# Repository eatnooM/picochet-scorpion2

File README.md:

# Picochet-Scorpion2

A dedicated microcontroller board for use with the OpenFIRE firmware, made to fit in the wonderfully comfortable Blaze Scorpion 2 shell

Picking up where the Picochet-TC1 left off, this board removes the solenoid feedback circuit and adds support for a few extra goodies that might make sense to add in a Scorpion 2, such as Neopixel LED (I have a 3D printable light pipe that takes the place of one of the wheels to adjust the laser in the stock Scorpion 2) and an analog stick (no plans to physically accommodate this in the shell but if you reckon you can make one fit, go nuts)

##  BOM

I'll copy the BOM into a nice table once it's settled.

## Thanks

OpenFIRE project - https://openfirelightgun.org/

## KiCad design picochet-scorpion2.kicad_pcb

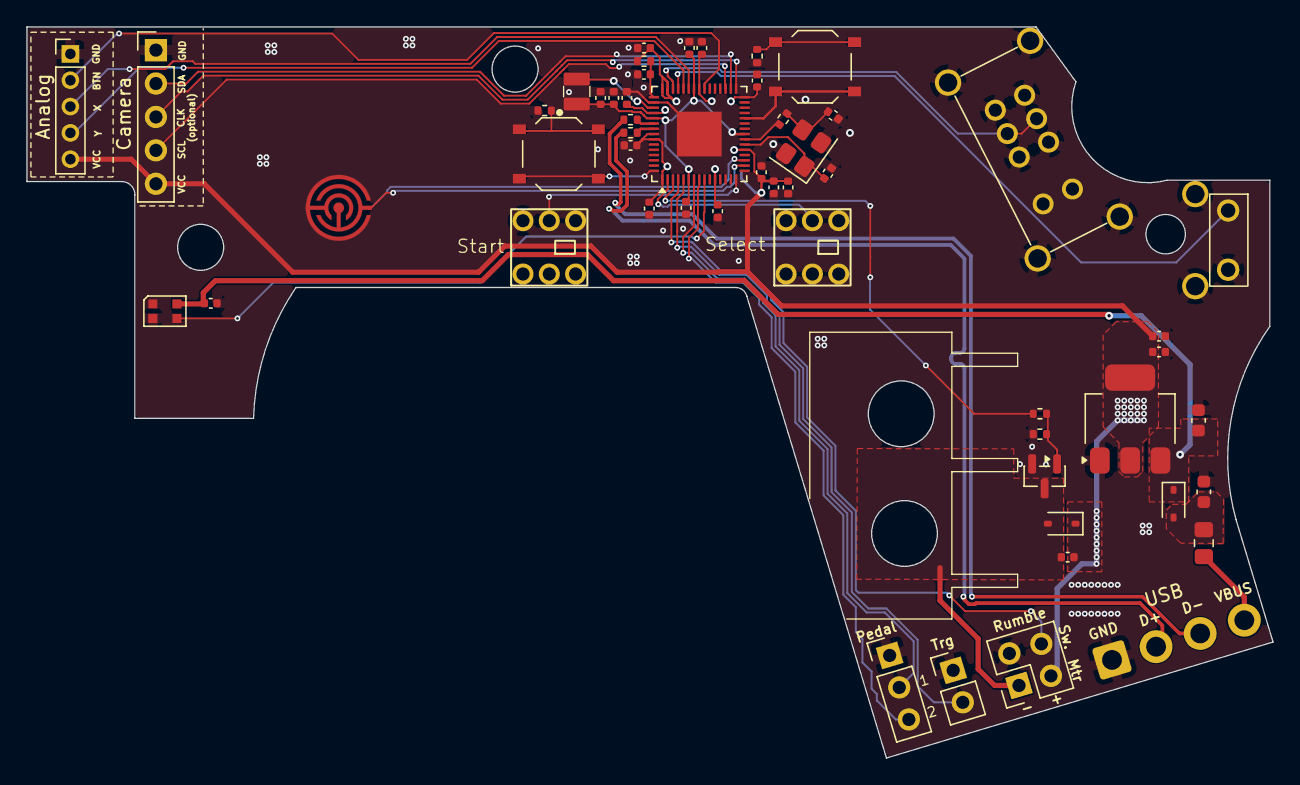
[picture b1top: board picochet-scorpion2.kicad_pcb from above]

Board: 2 copper layers, 94.7 x 55.6 mm, 54 parts (1 on the bottom side), 39 nets.

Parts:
C1, C21: 10uF; C_0603_1608Metric
C3, C4: 30pF; C_0402_1005Metric
C5, C19: 10uF; C_0402_1005Metric
C6, C7, C9, C10: 4.7uF; C_0402_1005Metric
C8, C11, C12, C13, C14, C15, C16, C17, C18, C20, C23, C24, C25: 100nF; C_0402_1005Metric
D1: 1N5819WS; D_SOD-323
D2: BAT43WS; D_SOD-323
D3: WS2812B-2020; LED_WS2812B-2020_PLCC4_2.0x2.0mm
F1: PPTC-6V 500mA; Fuse_0805_2012Metric_Pad1.15x1.40mm_HandSolder
J1: Conn_02x02; PinHeader_2x02_P2.54mm_Vertical
J2: Conn_01x02; PinHeader_1x02_P2.54mm_Vertical
J3: Conn_01x04; USB-PTH-2.5MMOD-3.5mmSpacing
J4: Conn_01x03; PinHeader_1x03_P2.54mm_Vertical
J6: Conn_01x05; PinHeader_1x05_P2.54mm_Vertical
J8: Conn_01x05; PinHeader_1x05_P2.00mm_Vertical
L1: AOTA-B201610S3R3; L_0806_PolarityMark
Q1: AO3400A; SOT-23
R2, R4, R6: 1k; R_0402_1005Metric
R5, R7, R8: 33; R_0402_1005Metric
R14: 100; R_0402_1005Metric
R15: 10k; R_0402_1005Metric
SW1, SW2: SW_Push; SW_Push_1P1T_XKB_TS-1187A
SW3: SW_SP3T_Shielded; ModeSwitch-DP3T-MountingPoints
SW4, SW5: SW_Push; RubberDomeContacts-D5mm
SW6: SW_Push; ModeSwitch-Momentary
SW7, SW8: SW_DPDT; Switch-DPDT-5.8x5.8mm
U1: RP2354A; QFN-60-1EP_7x7mm_P0.4mm_EP3.4x3.4mm
U2: AMS1117-3.3; SOT-223-3_TabPin2
Y1: X322512MSB4SI; Crystal_SMD_3225-4Pin_3.2x2.5mm

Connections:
+1V1: C7.1, C8.2, C10.1, C11.2, L1.1, U1.6 (DVDD), U1.23 (DVDD), U1.39 (DVDD), U1.50 (VREG_FB)
+3V3: C5.1, C6.1, C12.1, C13.1, C14.1, C15.1, C16.1, C17.1, C18.1, C19.1, C20.1, C24.1, C25.2, D2.1 (K), J1.3, J6.5, J8.5, R5.1, U1.1 (IOVDD), U1.11 (IOVDD), U1.20 (IOVDD), U1.30 (IOVDD), U1.38 (IOVDD), U1.44 (ADC_AVDD), U1.45 (IOVDD), U1.49 (VREG_VIN), U1.53 (USB_OTP_VDD), U1.54 (QSPI_IOVDD), U2.2 (VO)
+5V: C21.1, D1.2 (A), F1.2
/AXIS_X: J8.3, U1.40 (GPIO26/ADC0)
/AXIS_Y: J8.4, U1.41 (GPIO27/ADC1)
/CAM_CLK: J6.3, U1.31 (GPIO19)
/CAM_SCL: J6.4, U1.33 (GPIO21)
/CAM_SDA: J6.2, U1.32 (GPIO20)
/LED_DI: D3.3 (DIN), U1.9 (GPIO6)
/RMB_GND: C24.2, D2.2 (A), J1.1, Q1.3 (D)
/RUMBLE: R14.1, U1.3 (GPIO1)
/USB_D+: J3.2, R7.1
/USB_D-: J3.3, R8.1
/VREG_LX: L1.2, U1.48 (VREG_LX)
/~AUTOFIRE: SW3.3, U1.43 (GPIO29/ADC3)
/~BTN_A: SW4.1, U1.17 (GPIO13)
/~BTN_B: SW5.1, U1.18 (GPIO14)
/~BTN_HOME: SW6.1, U1.42 (GPIO28/ADC2)
/~BTN_PEDAL_ALT: J4.3, U1.8 (GPIO5)
/~BTN_PEDAL: J4.2, U1.7 (GPIO4)
/~BTN_SELECT: SW8.5 (B), U1.2 (GPIO0)
/~BTN_START: SW7.5 (B), U1.15 (GPIO11)
/~BTN_STICK: J8.2, U1.37 (GPIO25)
/~BTN_TRIGGER: J2.2, U1.5 (GPIO3)
/~RESET: SW2.2, U1.26 (RUN)
/~RMB_ENABLE: J1.4, U1.4 (GPIO2)
GND: C1.2, C3.1, C4.1, C5.2, C6.2, C7.2, C8.1, C9.2, C10.2, C11.1, C12.2, C13.2, C14.2, C15.2, C16.2, C17.2, C18.2, C19.2, C20.2, C21.2, C23.2, C25.1, D3.2 (VSS), J1.2, J2.1, J3.1, J4.1, J6.1, J8.1, Q1.2 (S), R4.1, R6.1, R15.2, SW3.2, SW3.4, SW3.SH, SW4.2, SW5.2, SW6.2, SW6.SH (B), SW7.4 (A), SW8.4 (A), U1.47 (VREG_PGND), U1.61 (GND), U2.1 (GND), Y1.2 (G), Y1.4 (G)
unnamed: C4.2, R2.2, Y1.3
unnamed: Q1.1 (G), R14.2, R15.1
unnamed: R4.2, SW2.1
unnamed: R6.2, SW1.1
unnamed: R8.2, U1.51 (USB_DM)
unnamed: R7.2, U1.52 (USB_DP)
unnamed: C3.2, U1.21 (XIN), Y1.1
unnamed: R2.1, U1.22 (XOUT)
unnamed: SW1.2, U1.60 (~QSPI_SS)
VBUS: F1.1, J3.4
VREG_AVDD: C9.1, R5.2, U1.46 (VREG_AVDD)
VSYS: C1.1, C23.1, D1.1 (K), D3.4 (VDD), U2.3 (VI)

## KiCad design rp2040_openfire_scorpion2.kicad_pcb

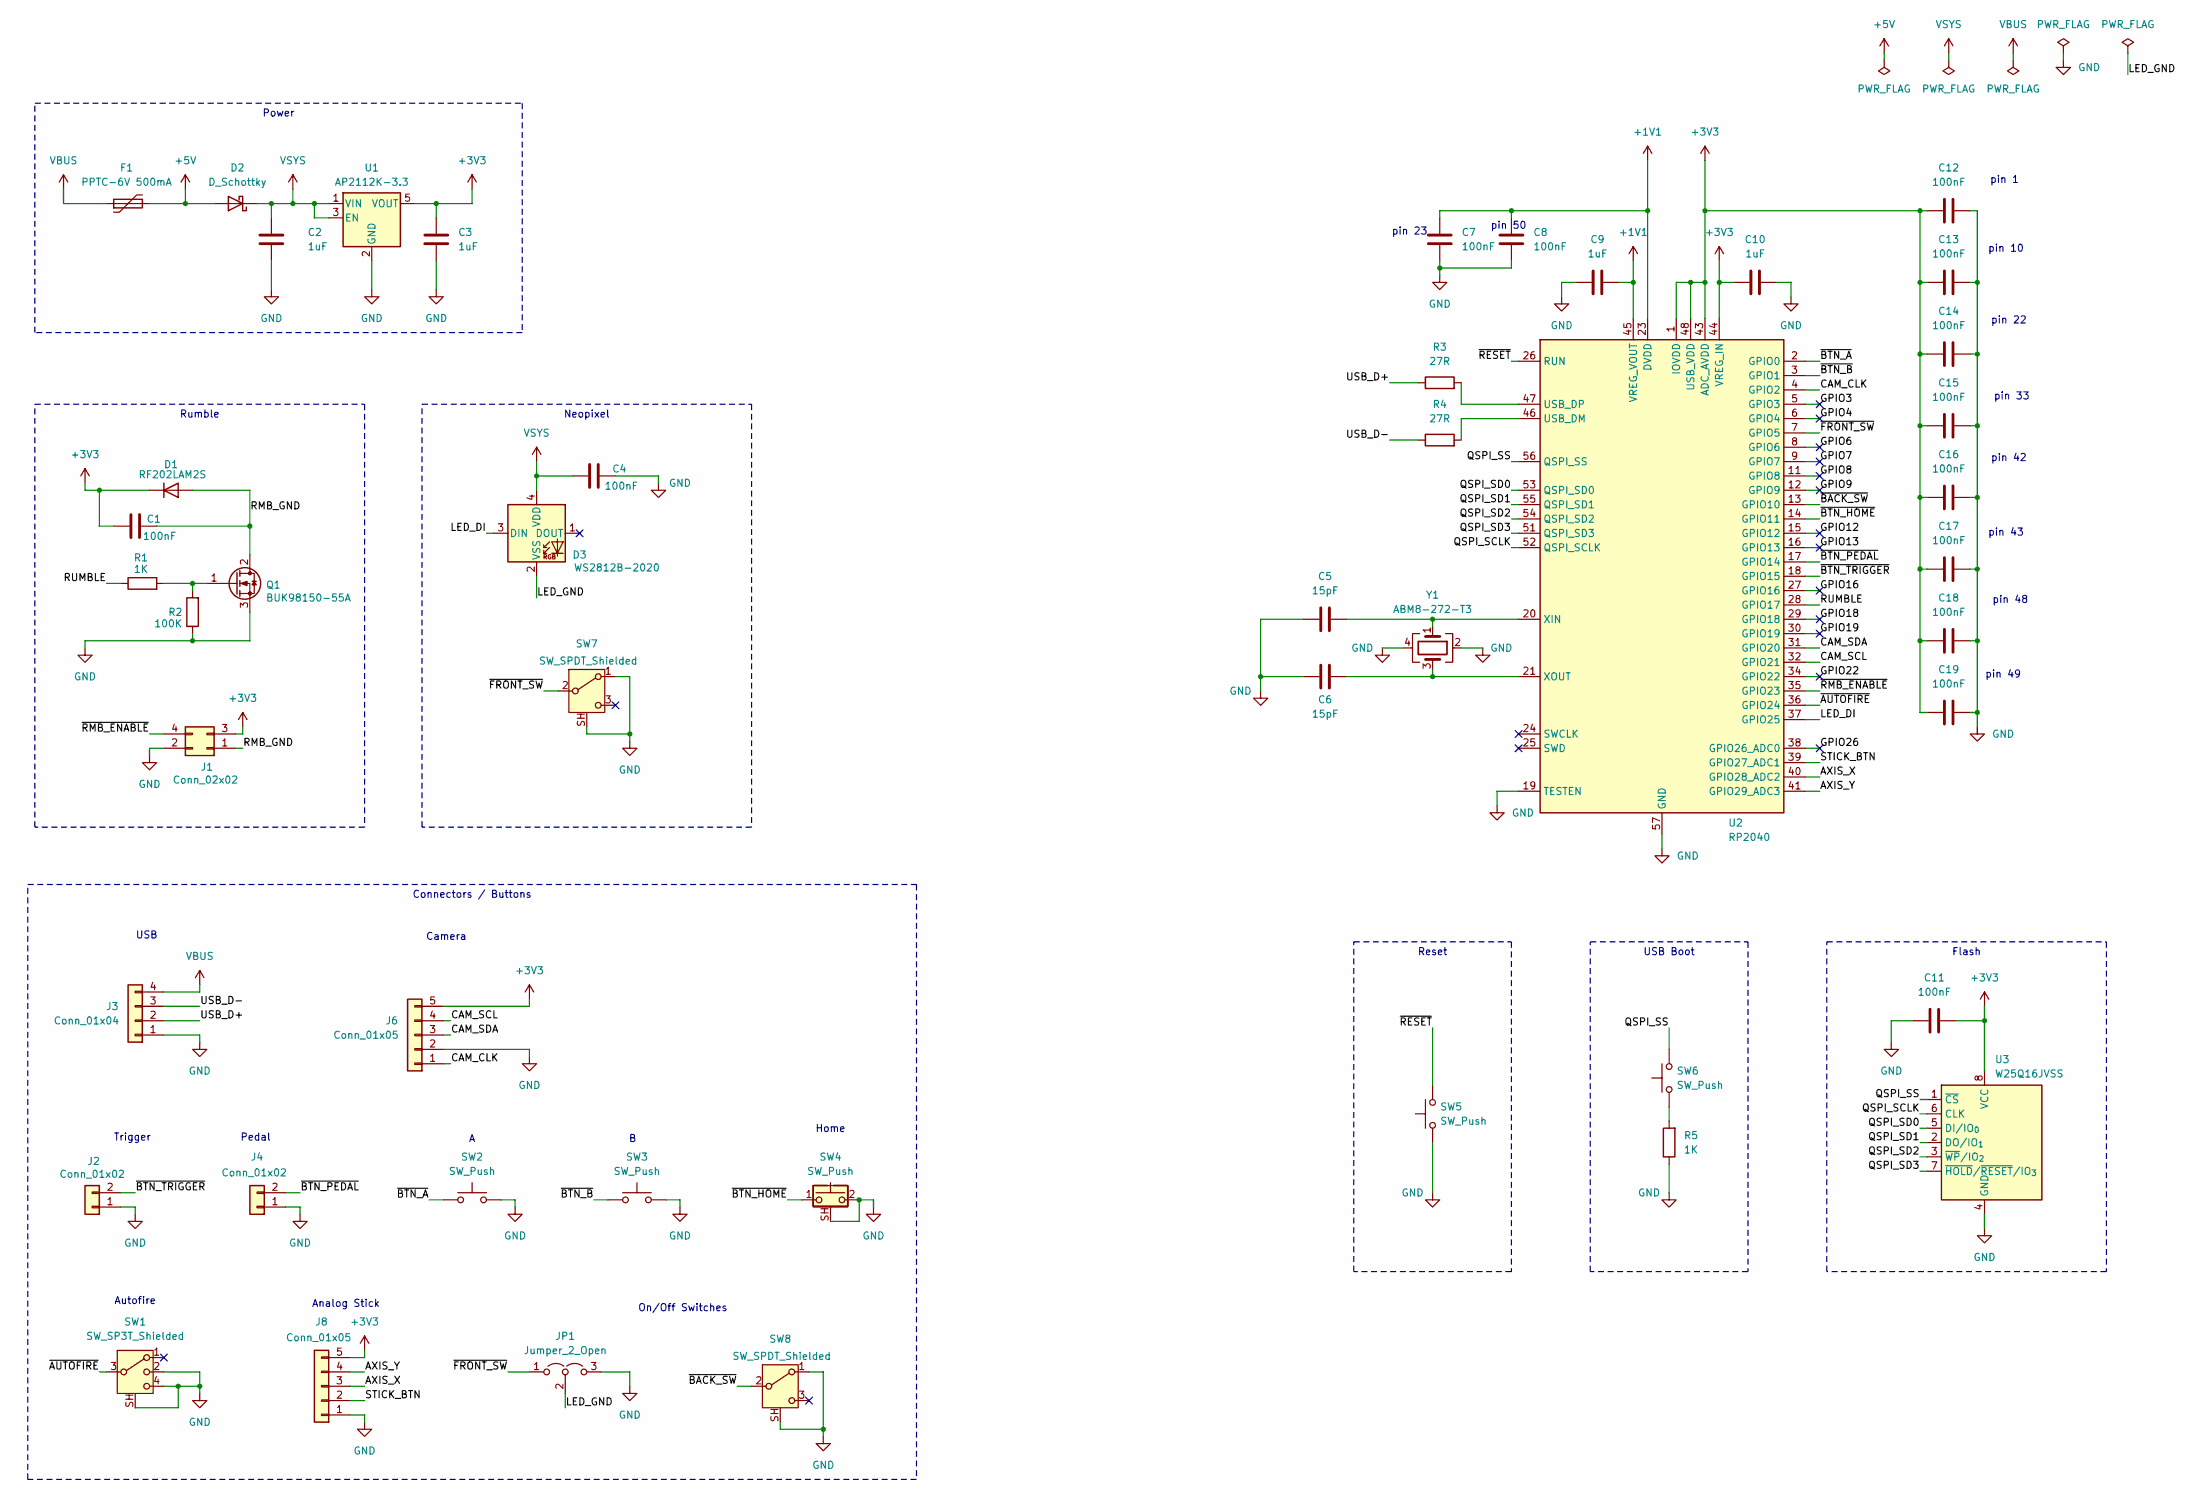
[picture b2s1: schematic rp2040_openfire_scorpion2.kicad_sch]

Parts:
C1, C4, C7, C8, C11, C12, C13, C14, C15, C16, C17, C18, C19: 100nF; C_0603_1608Metric_Pad1.08x0.95mm_HandSolder
C2, C3, C9, C10: 1uF; C_0603_1608Metric_Pad1.08x0.95mm_HandSolder
C5, C6: 15pF; C_0603_1608Metric_Pad1.08x0.95mm_HandSolder
D1: RF202LAM2S; D_SOD-128
D2: D_Schottky; D_SOD-323F
D3: WS2812B-2020; LED_WS2812B-2020_PLCC4_2.0x2.0mm
F1: PPTC-6V 500mA; Fuse_0805_2012Metric_Pad1.15x1.40mm_HandSolder
J1: Conn_02x02; PinHeader_2x02_P2.54mm_Vertical
J2, J4: Conn_01x02; PinHeader_1x02_P2.54mm_Vertical
J3: Conn_01x04; USB-PTH-2.5MMOD-3.5mmSpacing
J6: Conn_01x05; PinHeader_1x05_P2.54mm_Vertical
J8: Conn_01x05; PinHeader_1x05_P2.00mm_Vertical
JP1: Jumper_2_Open; SolderJumper-3_P1.3mm_Open_RoundedPad1.0x1.5mm_NumberLabels
Q1: BUK98150-55A; SOT-223-3_TabPin2
R1, R5: 1K; R_0603_1608Metric_Pad0.98x0.95mm_HandSolder
R2: 100K; R_0603_1608Metric_Pad0.98x0.95mm_HandSolder
R3, R4: 27R; R_0603_1608Metric_Pad0.98x0.95mm_HandSolder
SW1: SW_SP3T_Shielded; ModeSwitch-DP3T-MountingPoints
SW2, SW3: SW_Push; RubberDomeContacts-D5mm
SW4: SW_Push; ModeSwitch-Momentary
SW5, SW6: SW_Push; Switch-Push-SMD-4mmx3mm
SW7, SW8: SW_SPDT_Shielded; ModeSwitch-SPDT-MountingPoints
U1: AP2112K-3.3; SOT-23-5
U2: RP2040; QFN-56-1EP_7x7mm_P0.4mm_EP3.2x3.2mm
U3: W25Q16JVSS; SOIC-8_5.3x5.3mm_P1.27mm
Y1: ABM8-272-T3; Crystal_SMD_3225-4Pin_3.2x2.5mm_HandSoldering

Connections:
+1V1: C7.2, C8.2, C9.2, U2.23 (DVDD), U2.45 (VREG_VOUT), U2.50 (DVDD)
+3V3: C1.2, C3.1, C10.2, C11.2, C12.2, C13.2, C14.2, C15.2, C16.2, C17.2, C18.2, C19.2, D1.1 (K), J1.3, J6.5, J8.5, U1.5 (VOUT), U2.1 (IOVDD), U2.10 (IOVDD), U2.22 (IOVDD), U2.33 (IOVDD), U2.42 (IOVDD), U2.43 (ADC_AVDD), U2.44 (VREG_IN), U2.48 (USB_VDD), U2.49 (IOVDD), U3.8 (VCC)
+5V: D2.2 (A), F1.2
/AXIS_X: J8.3, U2.40 (GPIO28_ADC2)
/AXIS_Y: J8.4, U2.41 (GPIO29_ADC3)
/CAM_CLK: J6.1, U2.4 (GPIO2)
/CAM_SCL: J6.4, U2.32 (GPIO21)
/CAM_SDA: J6.3, U2.31 (GPIO20)
/GPIO3: U2.5 (GPIO3)
/GPIO4: U2.6 (GPIO4)
/GPIO6: U2.8 (GPIO6)
/GPIO7: U2.9 (GPIO7)
/GPIO8: U2.11 (GPIO8)
/GPIO9: U2.12 (GPIO9)
/GPIO12: U2.15 (GPIO12)
/GPIO13: U2.16 (GPIO13)
/GPIO16: U2.27 (GPIO16)
/GPIO18: U2.29 (GPIO18)
/GPIO19: U2.30 (GPIO19)
/GPIO22: U2.34 (GPIO22)
/GPIO26: U2.38 (GPIO26_ADC0)
/LED_DI: D3.3 (DIN), U2.37 (GPIO25)
/LED_GND: D3.2 (VSS), JP1.2 (C)
/QSPI_SCLK: U2.52 (QSPI_SCLK), U3.6 (CLK)
/QSPI_SD0: U2.53 (QSPI_SD0), U3.5 (DI/IO_{0})
/QSPI_SD1: U2.55 (QSPI_SD1), U3.2 (DO/IO_{1})
/QSPI_SD2: U2.54 (QSPI_SD2), U3.3 (~WP/IO_{2})
/QSPI_SD3: U2.51 (QSPI_SD3), U3.7 (~HOLD/~RESET/IO_{3})
/QSPI_SS: SW6.2, U2.56 (QSPI_SS), U3.1 (~CS)
/RMB_GND: C1.1, D1.2 (A), J1.1, Q1.2 (D)
/RUMBLE: R1.1, U2.28 (GPIO17)
/STICK_BTN: J8.2, U2.39 (GPIO27_ADC1)
/USB_D+: J3.2, R3.1
/USB_D-: J3.3, R4.1
/~AUTOFIRE: SW1.3, U2.36 (GPIO24)
/~BACK_SW: SW8.2, U2.13 (GPIO10)
/~BTN_A: SW2.1, U2.2 (GPIO0)
/~BTN_B: SW3.1, U2.3 (GPIO1)
/~BTN_HOME: SW4.1, U2.14 (GPIO11)
/~BTN_PEDAL: J4.2, U2.17 (GPIO14)
/~BTN_TRIGGER: J2.2, U2.18 (GPIO15)
/~FRONT_SW: JP1.1 (A), SW7.2, U2.7 (GPIO5)
/~RESET: SW5.2, U2.26 (RUN)
/~RMB_ENABLE: J1.4, U2.35 (GPIO23)
GND: C2.2, C3.2, C4.1, C5.1, C6.1, C7.1, C8.1, C9.1, C10.1, C11.1, C12.1, C13.1, C14.1, C15.1, C16.1, C17.1, C18.1, C19.1, J1.2, J2.1, J3.1, J4.1, J6.2, J8.1, JP1.3 (B), Q1.3 (S), R2.1, R5.1, SW1.2, SW1.4, SW1.SH, SW2.2, SW3.2, SW4.2, SW4.SH (B), SW5.1, SW7.1, SW7.SH, SW8.1, SW8.SH, U1.2 (GND), U2.19 (TESTEN), U2.57 (GND), U3.4 (GND), Y1.2, Y1.4
unnamed: Q1.1 (G), R1.2, R2.2
unnamed: R5.2, SW6.1
unnamed: R4.2, U2.46 (USB_DM)
unnamed: R3.2, U2.47 (USB_DP)
unnamed: C5.2, U2.20 (XIN), Y1.1
unnamed: C6.2, U2.21 (XOUT), Y1.3
VBUS: F1.1, J3.4
VSYS: C2.1, C4.2, D2.1 (K), D3.4 (VDD), U1.1 (VIN), U1.3 (EN)

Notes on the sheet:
Autofire
Camera
pin 43
Pedal
Analog Stick
pin 49
Trigger
Home
pin 10
pin 48
On/Off Switches
pin 1
pin 33
pin 50
USB
pin 42
pin 23
pin 22
Rumble
USB Boot
Neopixel
Reset
Power
Flash
Connectors / Buttons

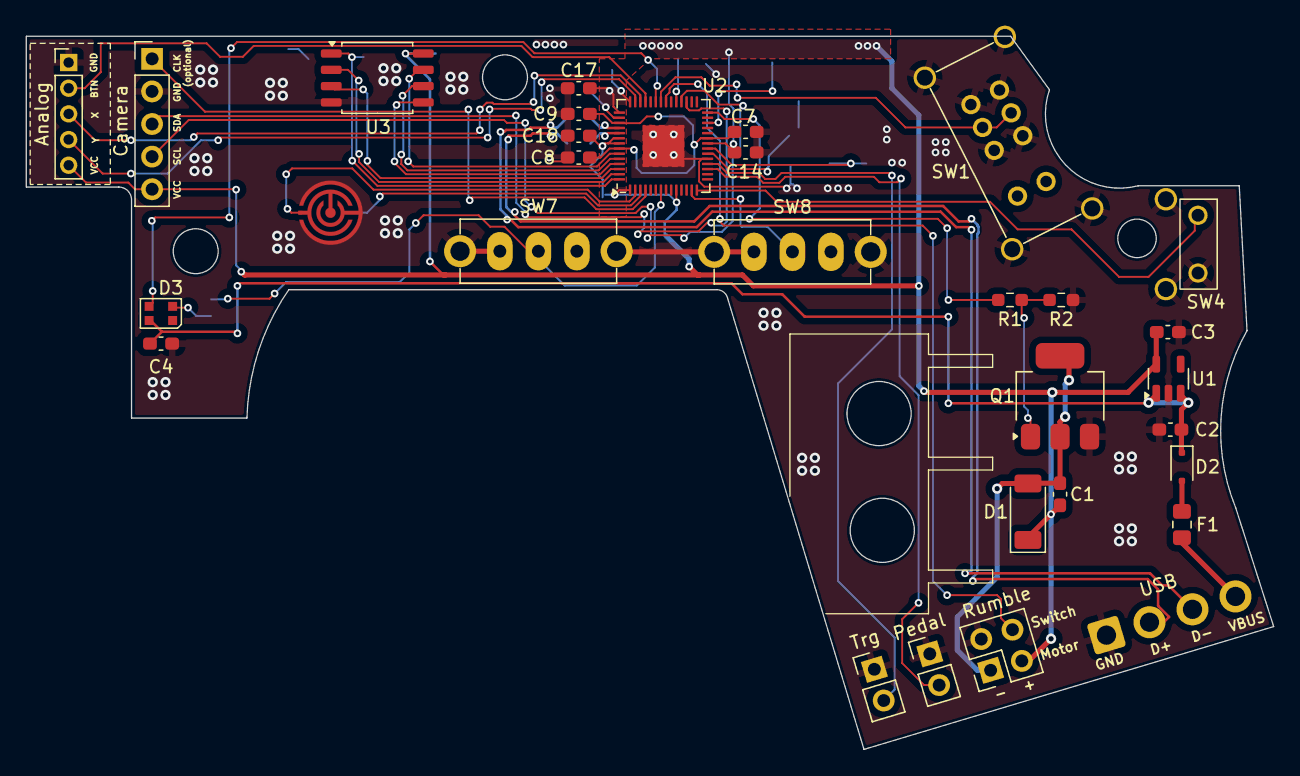
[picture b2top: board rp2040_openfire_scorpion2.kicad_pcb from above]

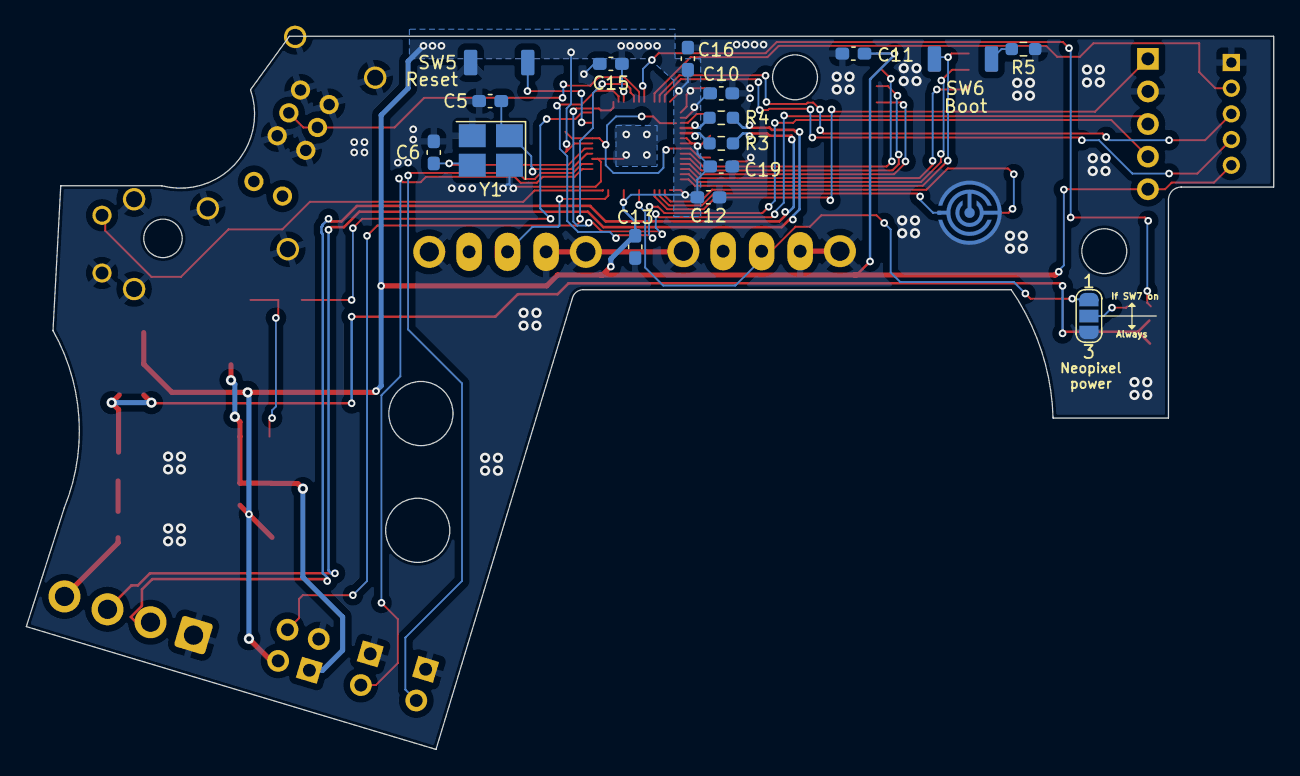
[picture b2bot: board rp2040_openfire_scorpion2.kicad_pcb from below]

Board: 2 copper layers, 97.2 x 55.6 mm, 48 parts (17 on the bottom side), 40 nets.

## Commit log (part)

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2026-05-23 Initial commit
    <_<
2026-05-24 v0.1 prototype
